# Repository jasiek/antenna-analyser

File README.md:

# antenna-analyser

There's a few projects like this one out there on the net. My goal was to create one that would be properly productized - eg.
with a PCB ready to be made and a parts list that can be easily obtained on eBay, etc.

The circuit is [K6BEZ's design](https://sites.google.com/site/k6bezprojects/antenna-analyser), and uses
an [Arduino Pro Mini](https://www.arduino.cc/en/Main/ArduinoBoardProMini), running at 8Mhz and 3.3V with
a cheap [SPI LCD TFT display](http://www.electrodragon.com/product/eds-tft-lcd-lcm-spi-interface-variable1-82-2)
to graphically represent the results of VSWR analysis.

I've bundled everything together into one repository so that the project can quickly be opened up in [KiCad](http://www.kicad-pcb.org/)
and the Arduino IDE.

## A few photos of the first prototype

## A few shots of the UI

## TODO

* Build and test this branch as a functional, physical prototype.
* ~~Improve menu structure and navigation.~~
* ~~Improve single band plot (move band label, min, max to the bottom). Notify the user when done plotting.~~
* When plotting all bands, plot amateur bands using a different colour.
* ~~Improve summary view, label columns, shorten frequency label.~~
* Add menu which lists 20 SWR minima across the band.

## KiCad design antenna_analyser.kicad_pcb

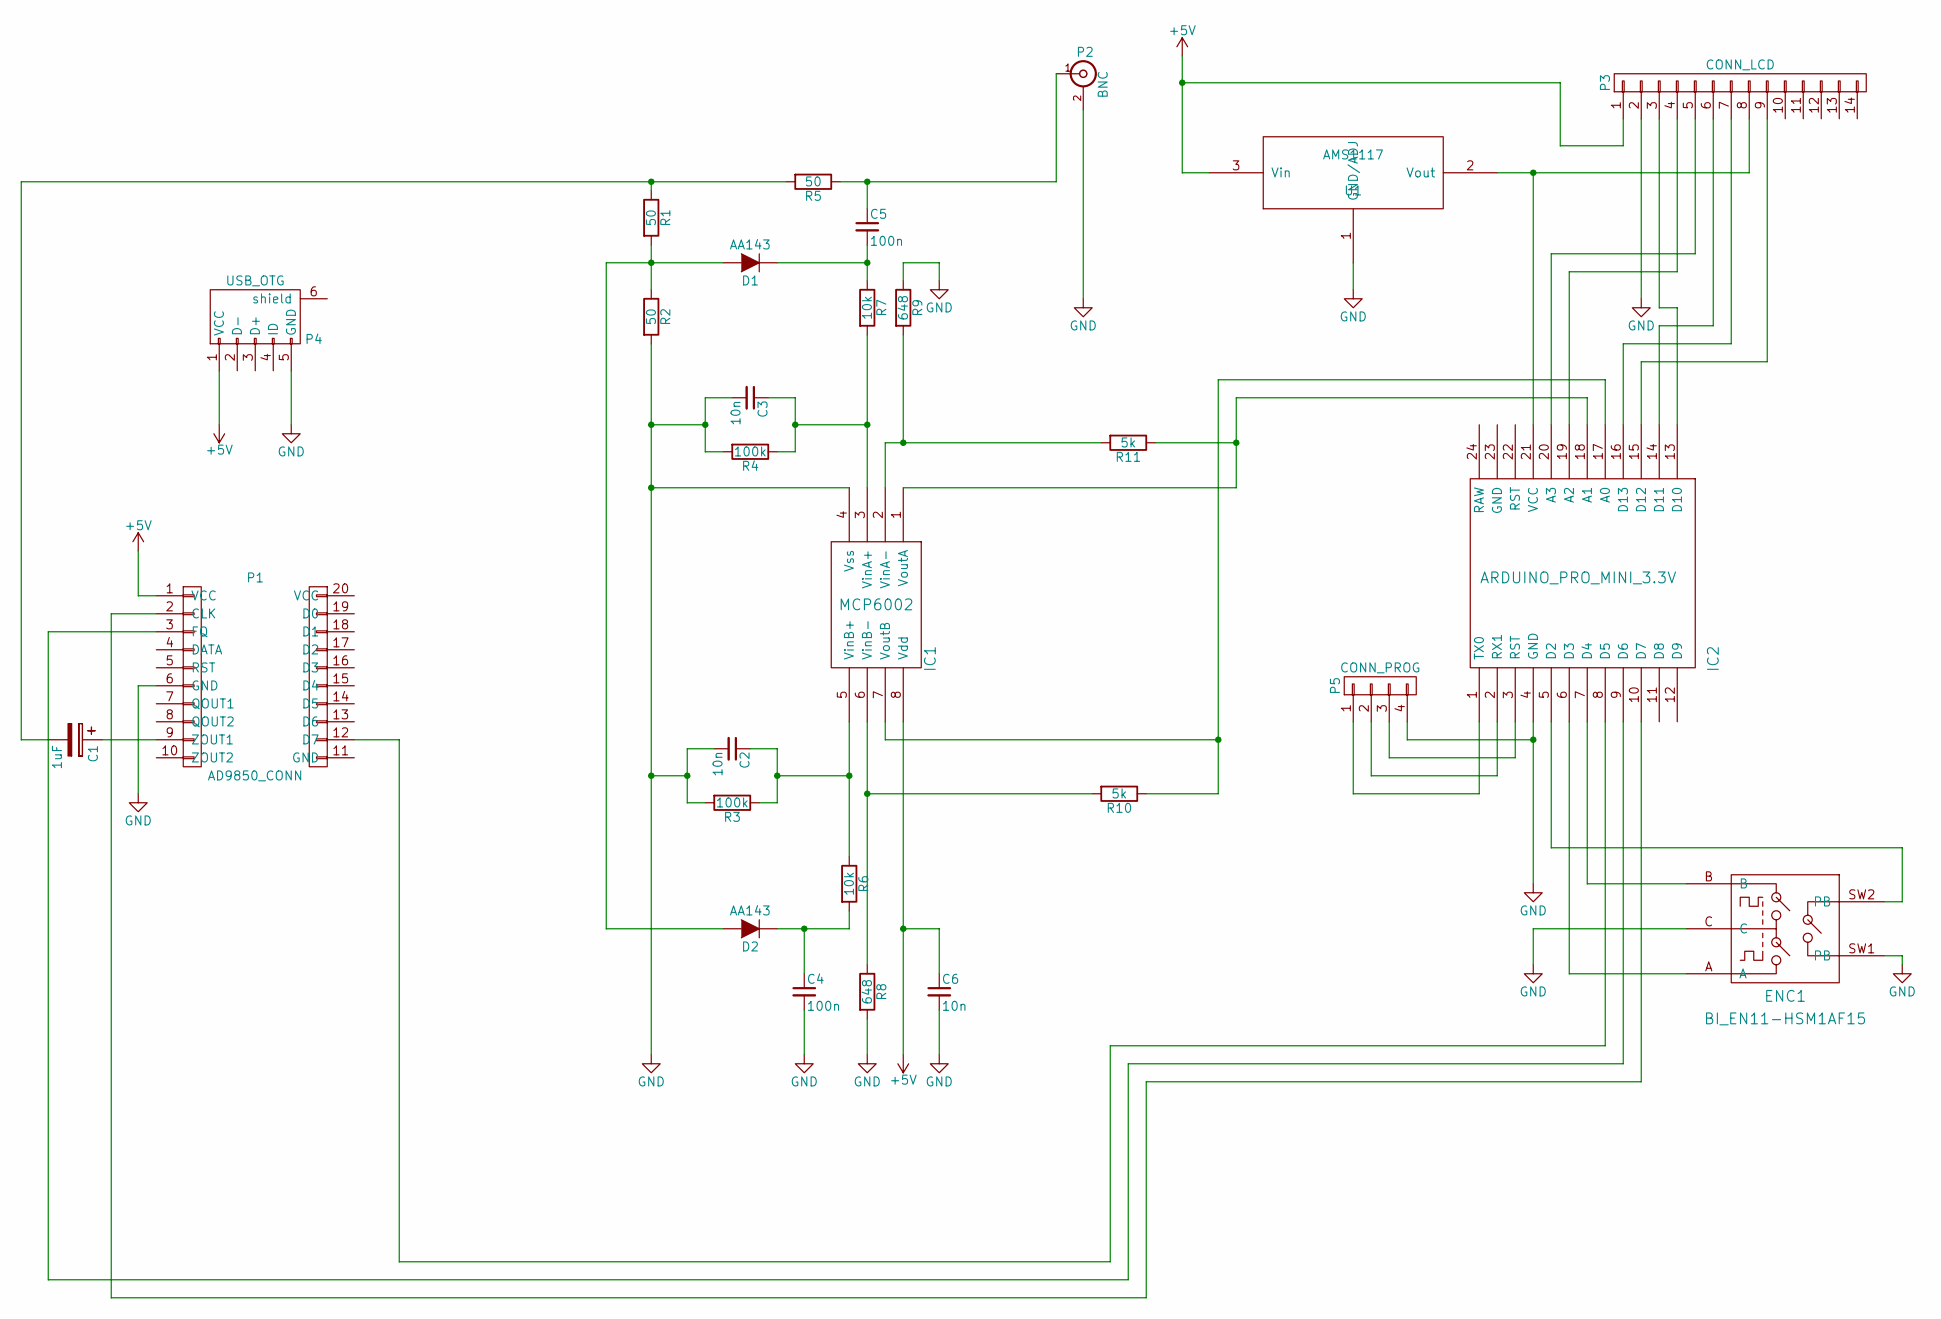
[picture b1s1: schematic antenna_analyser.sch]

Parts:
C1: 1uF; Elko_vert_20x10mm_RM2.5
C2, C3, C6: 10n; C_Disc_D3_P2.5
C4, C5: 100n; C_Disc_D3_P2.5
D1, D2: AA143; Diode_DO-41_SOD81_Horizontal_RM10
ENC1: BI_EN11-HSM1AF15; BI_EN12-HS22AF30
IC1: MCP6002; DIP-8_W7.62mm
IC2: ARDUINO_PRO_MINI_3.3V; ARDUINO_PRO_MINI
P1: AD9850_CONN; DDS_AD9850
P2: BNC; bnc-ci
P3: CONN_LCD; Socket_Strip_Straight_1x14
P4: USB_OTG; USB_Micro-B
P5: CONN_PROG; Socket_Strip_Straight_1x04
R1, R2, R5: 50; Resistor_Horizontal_RM10mm
R3, R4: 100k; Resistor_Horizontal_RM10mm
R6, R7: 10k; Resistor_Horizontal_RM10mm
R8, R9: 648; Resistor_Horizontal_RM10mm
R10, R11: 5k; Resistor_Horizontal_RM10mm
U1: AMS1117; SOT223

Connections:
+5V: C6.1, IC1.8 (Vdd), P1.1 (VCC), P3.1, P4.1 (VCC), U1.3 (Vin)
GND: C2.2, C3.2, C4.2, C6.2, ENC1.C, ENC1.SW1 (PB), IC1.4 (Vss), IC2.4 (GND), P1.6 (GND), P2.2 (Ext), P3.2, P4.5 (GND), P5.4, R2.2, R3.2, R4.2, R8.2, R9.1, U1.1 (GND/ADJ)
unnamed: C1.1, P1.9 (ZOUT1)
unnamed: C1.2, R1.1, R5.2
unnamed: C2.1, IC1.5 (VinB+), R3.1, R6.1
unnamed: C3.1, IC1.3 (VinA+), R4.1, R7.2
unnamed: C4.1, D2.1 (K), R6.2
unnamed: C5.1, P2.1 (In), R5.1
unnamed: C5.2, D1.1 (K), R7.1
unnamed: D1.2 (A), D2.2 (A), R1.2, R2.1
unnamed: ENC1.A, IC2.6 (D3)
unnamed: ENC1.B, IC2.7 (D4)
unnamed: ENC1.SW2 (PB), IC2.5 (D2)
unnamed: IC1.1 (VoutA), IC2.18 (A1), R11.1
unnamed: IC1.2 (VinA-), R9.2, R11.2
unnamed: IC1.6 (VinB-), R8.1, R10.2
unnamed: IC1.7 (VoutB), IC2.17 (A0), R10.1
unnamed: IC2.1 (TX0), P5.1
unnamed: IC2.2 (RX1), P5.2
unnamed: IC2.3 (RST), P5.3
unnamed: IC2.8 (D5), P1.12 (D7)
unnamed: IC2.9 (D6), P1.3 (FQ)
unnamed: IC2.10 (D7), P1.2 (CLK)
unnamed: IC2.13 (D10), P3.3
unnamed: IC2.14 (D11), P3.6
unnamed: IC2.15 (D12), P3.9
unnamed: IC2.16 (D13), P3.7
unnamed: IC2.19 (A2), P3.4
unnamed: IC2.20 (A3), P3.5
unnamed: IC2.21 (VCC), P3.8, U1.2 (Vout)

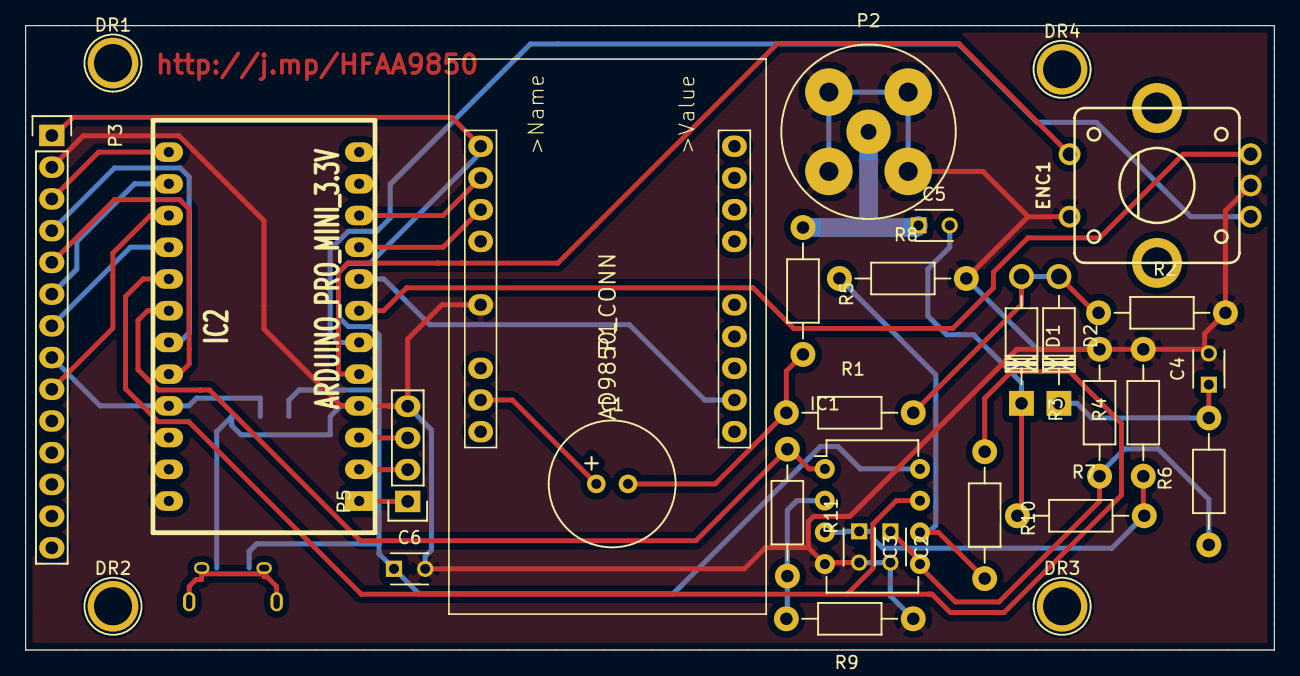
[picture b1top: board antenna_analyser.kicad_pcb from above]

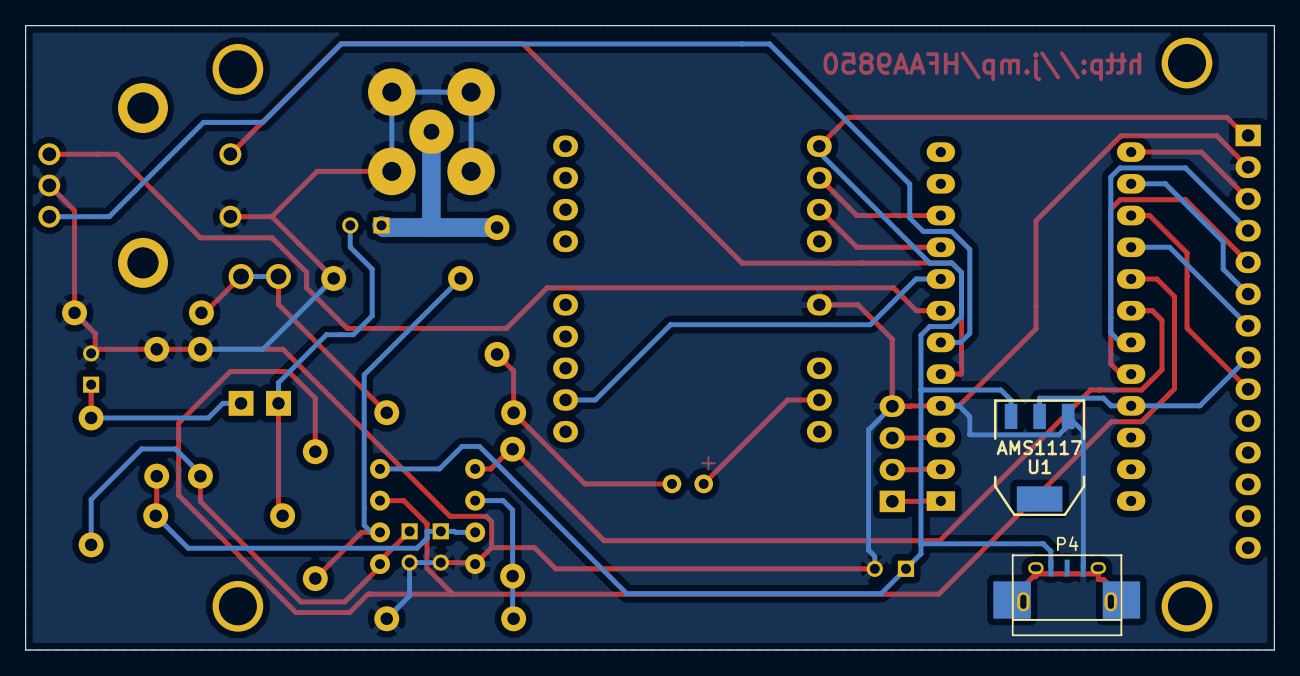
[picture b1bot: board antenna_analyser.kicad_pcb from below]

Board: 2 copper layers, 100.0 x 50.0 mm, 32 parts (2 on the bottom side), 30 nets.

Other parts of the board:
DR1, DR2, DR3, DR4: 1pin

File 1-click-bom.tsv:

References	Qty	Description
C1	1	CP 1uF Polarised capacitor Elko vert 20x10mm RM2.5
C3, C6, C2	3	C Small 10n Unpolarized capacitor Disc D3 P2.5
C5, C4	2	C Small 100n Unpolarized capacitor Disc D3 P2.5
D1, D2	2	D AA143 Diode DO-41 SOD81 Horizontal RM10
ENC1	1	BI EN11-HSM1AF15 Rotary encoder with switch EN12-HS22AF30
IC1	1	MCP6002-RESCUE-antenna analyser MCP6002 DIP-8 W7.62mm
IC2	1	ARDUINO PRO MINI 3.3V Arduino Pro Mini 5V 16MHz
P1	1	AD9850 CONN DDS
P2	1	BNC bnc-ci
P3	1	CONN 01X14 LCD Connector, single row, 01x14, pin header Socket Strip Straight 1x14
P4	1	USB OTG-RESCUE-antenna analyser OTG Micro-B
P5	1	CONN 01X04 PROG Connector, single row, 01x04, pin header Socket Strip Straight 1x04
R2, R1, R5	3	R 50 Resistor Horizontal RM10mm
R4, R3	2	R 100k Resistor Horizontal RM10mm
R7, R6	2	R 10k Resistor Horizontal RM10mm
R9, R8	2	R 648 Resistor Horizontal RM10mm
R10, R11	2	R 5k Resistor Horizontal RM10mm
U1	1	AMS1117 SOT223

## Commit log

2015-06-05 Updated element references and their values.
2015-06-24 Minor updates.
2015-06-24 Squashed 'libs/0xANDREW/' content from commit c938529
    git-subtree-dir: libs/0xANDREW
    git-subtree-split: c9385298970ce8d5b4081266b107748193f8bd81
2015-06-24 Updated library references.
2015-06-24 Added Edge SMA connectors library from:
    http://www.kicadlib.org/modules/JOS_SMA_connectors.zip
2015-06-24 The antenna connector is an SMA edge connector now.
2015-06-24 Squashed 'libs/jasiek/' content from commit c7b7a3a
    git-subtree-dir: libs/jasiek
    git-subtree-split: c7b7a3a78ed0fb45c8dd56f6ba5fb27df050de2e
2015-06-24 The MCP6002 part now references footprints I designed for a breakout board.
2015-06-24 Added a footprint library for the AD9850 from here:
    http://nyfiken.org/arkiv/402
2015-06-26 Squashed 'libs/nekromant/' content from commit 48787e1
    git-subtree-dir: libs/nekromant
    git-subtree-split: 48787e1932749e55301ef541aca51f706fdd1ddc
2015-06-26 Squashed 'libs/joeferner/' content from commit 5b82d79
    git-subtree-dir: libs/joeferner
    git-subtree-split: 5b82d79c0b26a85290f9922229c9e97191bc9abf
2015-06-26 Ignore .DS_Store
2015-06-26 Added Arduino Pro Mini footprints from:
    http://www.kicadcloud.com/pcbModule/4420
2015-06-26 Added an Arduino and a voltage regulator to the schematics.
2015-06-28 Added a footprint library entry for the AD9850 module.
2015-06-28 Updates to the schematic.
    Replaced 50ohm and 5kohm resistors with their equivalent parallel circuits.
    Added an AD9850 module to the schematic for easier reference.
2015-07-01 I can now draw a single line across the display.
2015-07-01 Draw a slight curve and a green dot wherever 0,0 is.
2015-07-02 Finished first screen which displays the frequency and SWR as text.
2015-07-02 Use hardware SPI instead (duh!).
2015-07-02 Added a second screen (vswr/f plot).
2015-07-04 Both screens are visible, SWR measuring routine is in.
2015-07-04 Added a connector for the LCD display.
2015-07-04 Added a rotary encoder library (might not be the right!) from:
    http://www.kicadlib.org/modules/KM_rotary-switch.zip
2015-07-04 Added a switch for changing modes of operation, and a rotary encoder to change the frequency.
2015-07-05 Updated code to display a plot of SWR versus frequency, and tested on my local antenna.
2015-07-06 Removed KM library.
2015-07-06 Squashed 'libs/madworm/' content from commit 87e31c1
    git-subtree-dir: libs/madworm
    git-subtree-split: 87e31c1ca5d03a644bb60bb8fde98b3ca718c410
2015-07-06 Moved to .pretty
2015-07-06 Added an edge connector for the rotary encoder.
2015-07-07 PCB first attempt, no luck. Need to make sure the elements are on the correct side.
2015-07-07 MCP6002 is now properly attached on the PCB. The arduino board is attached as well. PCB needs work to be one-sided only.
2015-07-07 Playing with freerouting, need to lay components according to a semi-planar schema and run freerouting on it.
2015-07-08 Added a photo of my prototype.
2015-07-08 Moving some components around so that freerouting can produce a single sided PCB.
2015-07-12 Use analog pins to have all LCD connectors on one side.
2015-07-12 50/5k ohm resistors
2015-07-14 Track laying, cont'd.
2015-07-15 Final PCB
2015-07-17 Added some pictures
2015-08-03 I'm experimenting with different UIs and different ways of displaying data.
2015-08-04 Initial version of menu navigation. Refresh rate is VERY LOW (bad).
2015-08-04 There are three options in the main menu, each is selectable using a rotary encoder + a click. Refresh rate is decent.
2015-08-04 All menus work flawlessly.
2015-08-04 Flattened menu structure. Each band can now be plotted directly from the menu.
2015-08-04 Readme updates.
2015-08-06 Improved UI for displaying plot of SWR vs frequency.
2015-08-06 Final touches on the UI.
2015-08-06 Added some pictures.
2015-08-08 Added a USB micro connector, and a 14-pin strip socket for the LCD.
2015-08-08 Added programming connector.
2015-08-08 Preliminary part layout
2015-08-09 Two-sided PCB with a USB connector and programming pins.
2015-08-09 Another 2-sided PCB interation, this time with mounting points.
2015-08-11 Straightened and simplified a couple of tracks.
2015-08-11 Embiggened pads on the AD9850, removed some pads to make way for tracks.
2015-08-11 Added a shortlink to the github site:
    http://j.mp/HFAA9850
2015-08-11 A few mods more.
2015-08-11 Production-ready PDFs (meant to be printed on the same page)
2015-08-11 Replot PDFs to get rid of reference marks.
2015-08-11 Final touches.
2015-08-12 Generated PDF schema.
2015-08-12 Added schematics and PCB shot.
2015-08-12 Better references to images.
2015-08-12 Small reorg.
2015-08-18 Added auxiliary soldering points to make it easier to attach the USB socket to the board.
2017-05-09 Production artifacts.
2017-06-02 Move code to PlatformIO
2017-06-02 Moved code into PlatformIO.
2017-06-02 Code compiles.
2018-03-08 Added metadata for kitspace.org
2018-03-08 Updated kitspace.yaml
2018-03-08 Reopened the project with 4.0.7 and regenerated drill files.
2018-03-08 Updated BOM.
